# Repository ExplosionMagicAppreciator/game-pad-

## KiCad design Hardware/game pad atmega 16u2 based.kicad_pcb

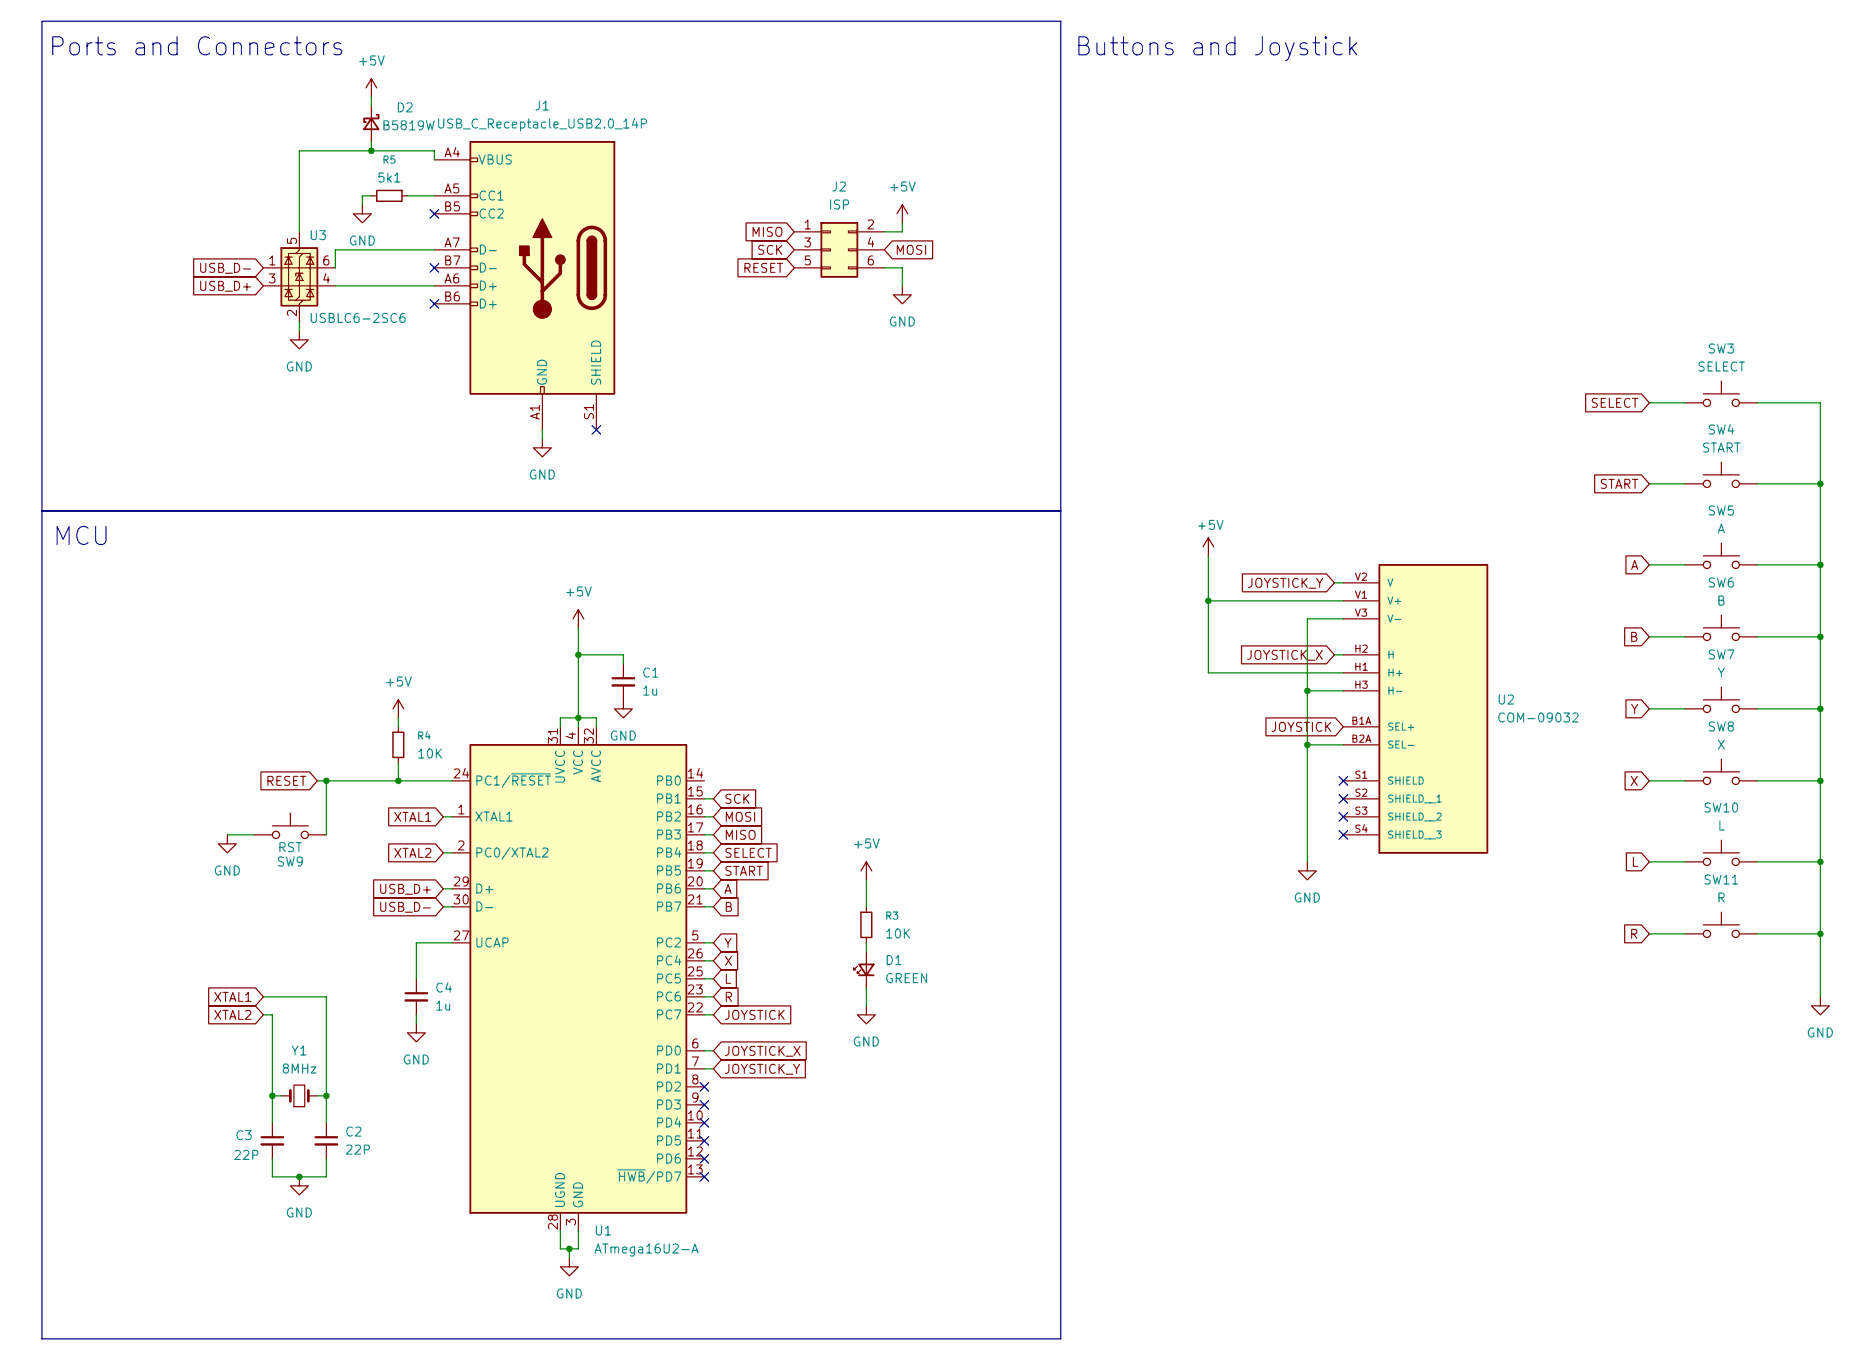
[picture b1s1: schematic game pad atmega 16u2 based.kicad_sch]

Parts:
C1, C4: 1u; C_0201_0603Metric
C2, C3: 22P; C_0201_0603Metric
D1: GREEN; LED_0603_1608Metric_Pad1.05x0.95mm_HandSolder
D2: B5819W; D_SOD-123
J1: USB_C_Receptacle_USB2.0_14P; USB_C_Receptacle_GCT_USB4105-xx-A_16P_TopMnt_Horizontal
J2: ISP; IDC-Header_2x03_P2.54mm_Horizontal
R3, R4: 10K; R_0603_1608Metric
R5: 5k1; R_0603_1608Metric
SW3: SELECT; SW_SPST_B3U-1000P-B
SW4: START; SW_SPST_B3U-1000P-B
SW5: A; membarine switch
SW6: B; membarine switch
SW7: Y; membarine switch
SW8: X; membarine switch
SW9: RST; SW_SPST_B3U-1000P-B
SW10: L; SW_Tactile_SPST_Angled_PTS645Vx39-2LFS
SW11: R; SW_Tactile_SPST_Angled_PTS645Vx39-2LFS
U1: ATmega16U2-A; TQFP-32_7x7mm_P0.8mm
U2: COM-09032; XDCR_COM-09032; PARTREV N/A
U3: USBLC6-2SC6; SOT-23-6
Y1: 8MHz; Crystal_SMD_5032-2Pin_5.0x3.2mm

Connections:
+5V: C1.1, D2.1 (K), J2.2, R3.1, R4.1, U1.4 (VCC), U1.31 (UVCC), U1.32 (AVCC), U2.H1 (H+), U2.V1 (V+)
A: SW5.1, U1.20 (PB6)
B: SW6.1, U1.21 (PB7)
GND: C1.2, C2.2, C3.2, C4.2, D1.1 (K), J1.A1 (GND), J1.A12 (GND), J1.B1 (GND), J1.B12 (GND), J2.6, R5.2, SW3.2, SW4.2, SW5.2, SW6.2, SW7.2, SW8.2, SW9.1, SW10.2, SW11.2, U1.3 (GND), U1.28 (UGND), U2.B2A (SEL-), U2.H3 (H-), U2.V3 (V-), U3.2 (GND)
JOYSTICK: U1.22 (PC7), U2.B1A (SEL+)
JOYSTICK_X: U1.6 (PD0), U2.H2 (H)
JOYSTICK_Y: U1.7 (PD1), U2.V2 (V)
L: SW10.1, U1.25 (PC5)
MISO: J2.1, U1.17 (PB3)
MOSI: J2.4, U1.16 (PB2)
unnamed: D1.2 (A), R3.2
unnamed: D2.2 (A), J1.A4 (VBUS), J1.A9 (VBUS), J1.B4 (VBUS), J1.B9 (VBUS), U3.5 (VBUS)
unnamed: J1.A5 (CC1), R5.1
unnamed: J1.A6 (D+), U3.4 (I/O2)
unnamed: J1.A7 (D-), U3.6 (I/O1)
unnamed: C4.1, U1.27 (UCAP)
R: SW11.1, U1.23 (PC6)
RESET: J2.5, R4.2, SW9.2, U1.24 (PC1/~RESET)
SCK: J2.3, U1.15 (PB1)
SELECT: SW3.1, U1.18 (PB4)
START: SW4.1, U1.19 (PB5)
USB_D+: U1.29 (D+), U3.3 (I/O2)
USB_D-: U1.30 (D-), U3.1 (I/O1)
X: SW8.1, U1.26 (PC4)
XTAL1: C2.1, U1.1 (XTAL1), Y1.2
XTAL2: C3.1, U1.2 (PC0/XTAL2), Y1.1
Y: SW7.1, U1.5 (PC2)

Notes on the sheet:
Buttons and Joystick
Ports and Connectors
MCU

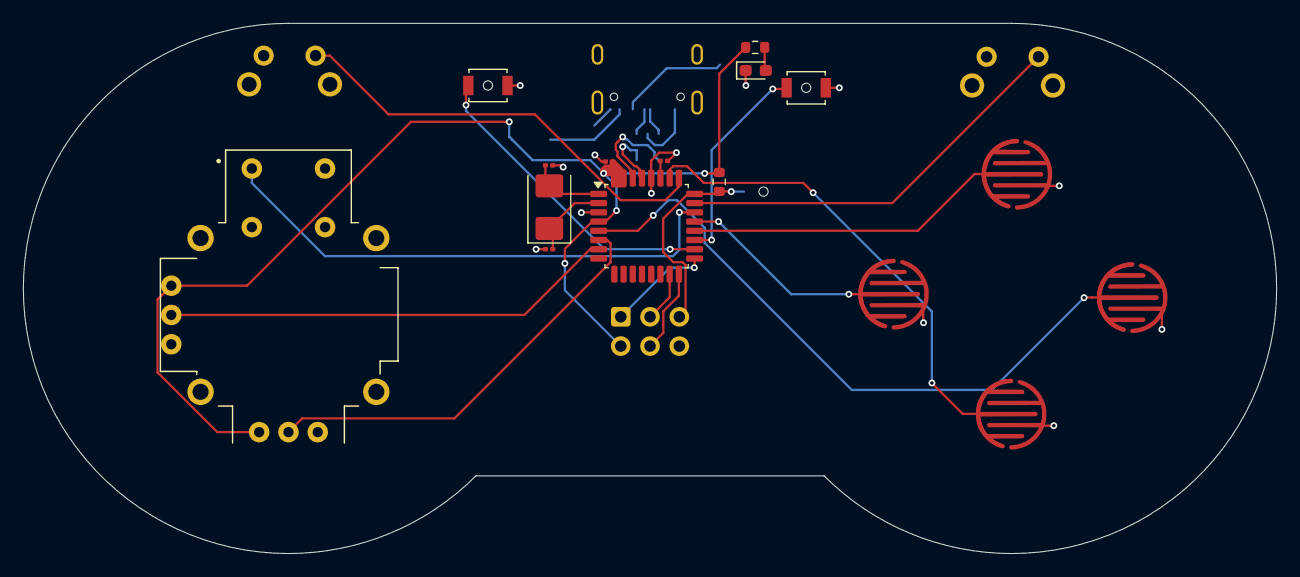
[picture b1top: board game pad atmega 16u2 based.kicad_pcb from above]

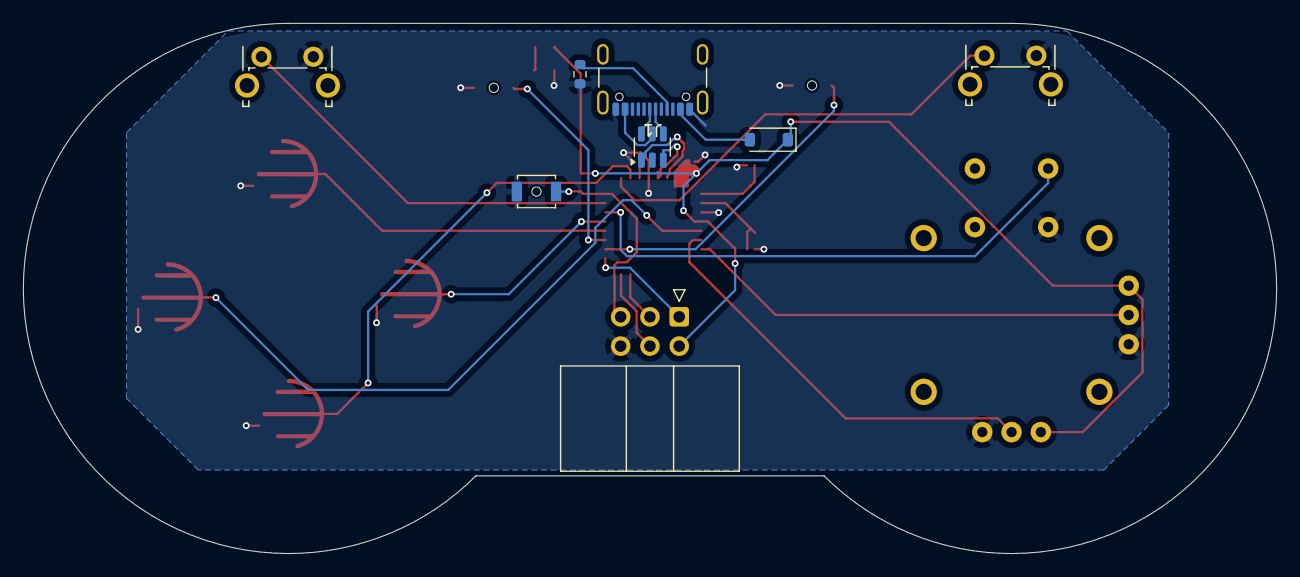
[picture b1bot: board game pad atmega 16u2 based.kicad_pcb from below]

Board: 2 copper layers, 108.7 x 46.0 mm, 24 parts (8 on the bottom side), 27 nets.

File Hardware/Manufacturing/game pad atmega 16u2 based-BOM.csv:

"Reference","Qty","Value","DNP","Exclude from BOM","Exclude from Board","Footprint","Datasheet"
"C1,C4","2","1u","","","","Capacitor_SMD:C_0201_0603Metric","~"
"C2,C3","2","22P","","","","Capacitor_SMD:C_0201_0603Metric","~"
"D1","1","GREEN","","","","LED_SMD:LED_0603_1608Metric_Pad1.05x0.95mm_HandSolder","~"
"D2","1","B5819W","","","","Diode_SMD:D_SOD-123","~"
"J1","1","USB_C_Receptacle_USB2.0_14P","","","","Connector_USB:USB_C_Receptacle_GCT_USB4105-xx-A_16P_TopMnt_Horizontal","https://www.usb.org/sites/default/files/documents/usb_type-c.zip"
"J2","1","ISP","","","","Connector_IDC:IDC-Header_2x03_P2.54mm_Horizontal","~"
"R3,R4","2","10K","","","","Resistor_SMD:R_0603_1608Metric","~"
"R5","1","5k1","","","","Resistor_SMD:R_0603_1608Metric","~"
"SW3","1","SELECT","","","","Button_Switch_SMD:SW_SPST_B3U-1000P-B","~"
"SW4","1","START","","","","Button_Switch_SMD:SW_SPST_B3U-1000P-B","~"
"SW5","1","A","","","","external libraries:membarine switch","~"
"SW6","1","B","","","","external libraries:membarine switch","~"
"SW7","1","Y","","","","external libraries:membarine switch","~"
"SW8","1","X","","","","external libraries:membarine switch","~"
"SW9","1","RST","","","","Button_Switch_SMD:SW_SPST_B3U-1000P-B","~"
"SW10","1","L","","","","Button_Switch_THT:SW_Tactile_SPST_Angled_PTS645Vx39-2LFS","~"
"SW11","1","R","","","","Button_Switch_THT:SW_Tactile_SPST_Angled_PTS645Vx39-2LFS","~"
"U1","1","ATmega16U2-A","","","","Package_QFP:TQFP-32_7x7mm_P0.8mm","http://ww1.microchip.com/downloads/en/DeviceDoc/doc7799.pdf"
"U2","1","COM-09032","","","","COM_09032:XDCR_COM-09032",""
"U3","1","USBLC6-2SC6","","","","Package_TO_SOT_SMD:SOT-23-6","https://www.st.com/resource/en/datasheet/usblc6-2.pdf"
"Y1","1","8MHz","","","","Crystal:Crystal_SMD_5032-2Pin_5.0x3.2mm","~"
